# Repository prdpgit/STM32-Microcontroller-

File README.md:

# STM32 Microcontroller 
 
The designed PCB features an STM32F4RTG6 microcontroller which is part of the STM32F4 series known for its high performance and with floating point unit (FPU) that supports ARM Cortex-M4 core. The board integrates an MPU6050, which is a popular 6-axis MotionTracking device combining a 3-axis gyroscope and a 3-axis accelerometer.

## Microcontroller Core:

STM32F4RTG6: ARM Cortex-M4 core with FPU, running at high frequencies, capable of driving complex applications that require floating-point calculations and advanced control algorithms.
Sensors:

MPU6050: Offers onboard Digital Motion Processing™ (DMP™) capable of processing complex 6-axis MotionFusion algorithms. The sensors communicate via I2C protocol, which is set up on the STM32F4 microcontroller.
Power Supply:

The board appears to have a +5V input power supply, with onboard voltage regulation to provide +3.3V needed by both the STM32 microcontroller and the MPU6050 sensor.
Voltage regulators (like AMS1117-3.3) are used to step down the voltage.
Various capacitors are placed near power inputs and voltage regulators to stabilize the power supply and reduce noise.
Connectivity:

The microcontroller’s I/O pins are brought out to headers, providing the ability to connect to other peripherals and sensors.
The schematic shows decoupling capacitors and pull-up resistors on I2C lines which are critical for signal integrity.
Programming and Debugging Interface:

There appears to be a programming interface, possibly using Serial Wire Debug (SWD), which is standard for STM32 devices. This allows for programming and debugging of the microcontroller directly on the board.
Oscillator:

A crystal oscillator is used for providing an accurate clock signal to the STM32F4 microcontroller.
Load capacitors are connected to the crystal to ensure proper oscillation.
General PCB Design Notes:

The schematic is organized into functional blocks, which simplifies the complexity and helps in understanding the circuit.
Each IC has decoupling capacitors close to the power supply pins to reduce power supply noise and for maintaining signal integrity.
The use of pull-up resistors on the reset line and buttons indicates attention to proper microcontroller reset and user input handling.

## Schematic:

## PCB layout

## 3D PCB render

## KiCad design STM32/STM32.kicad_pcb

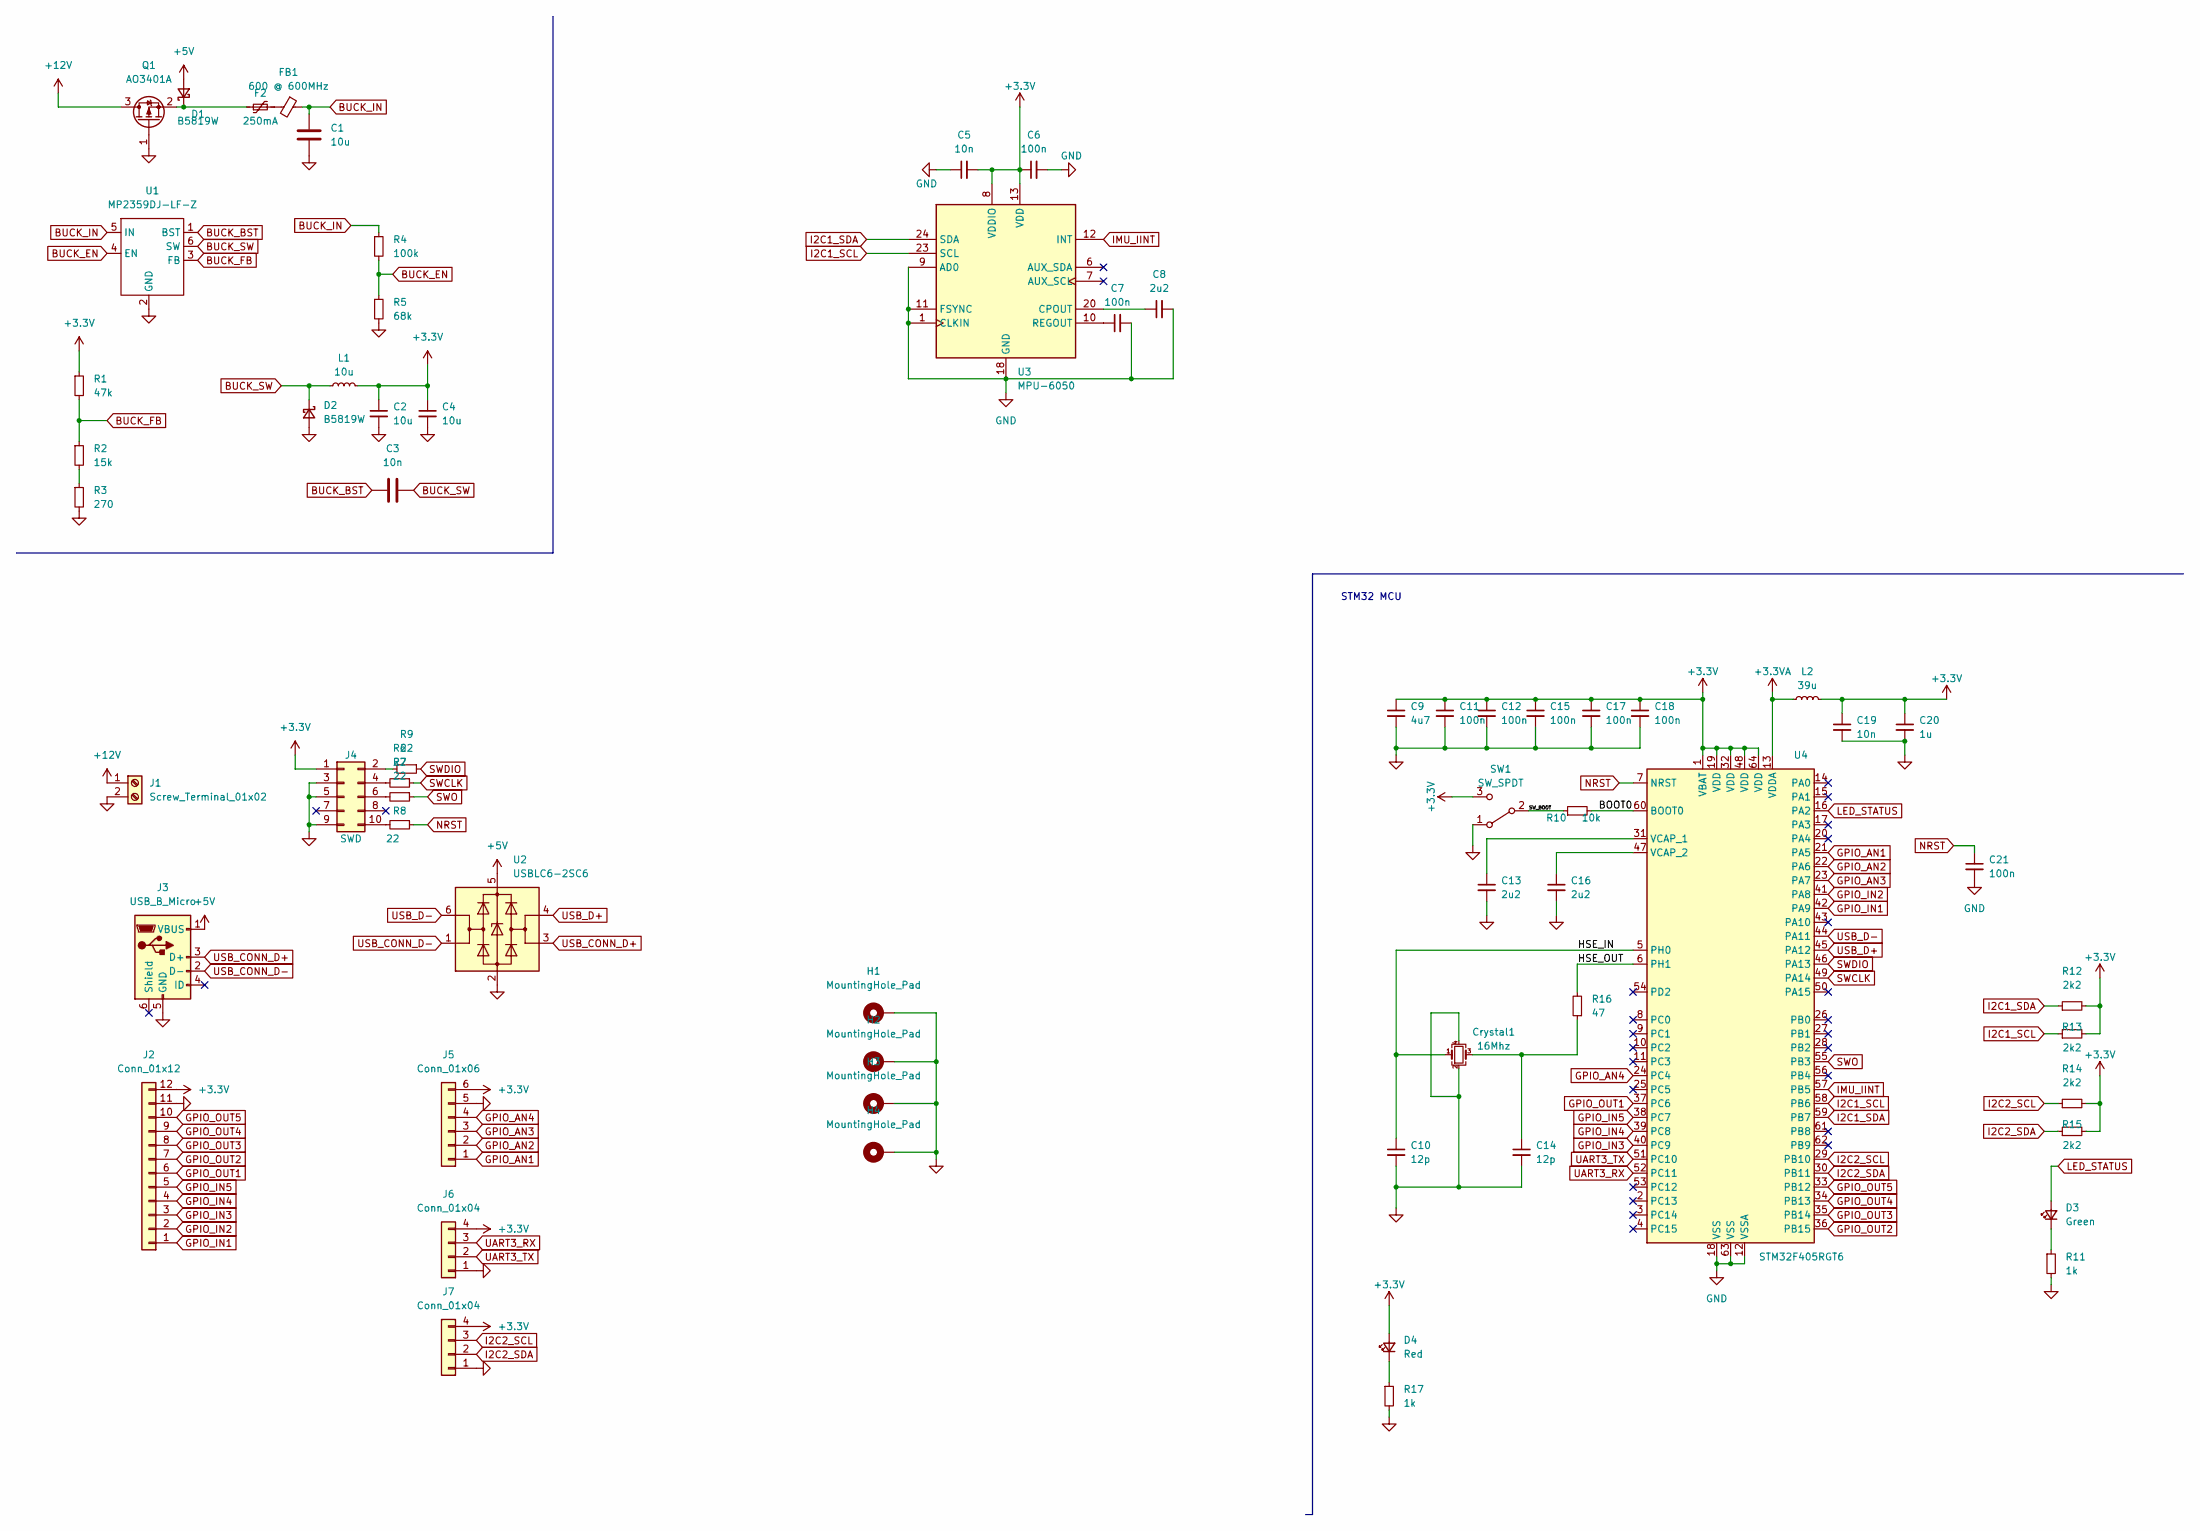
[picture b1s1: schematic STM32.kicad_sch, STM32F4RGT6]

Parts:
C1, C2, C4: 10u; C_1206_3216Metric; LCSC Part # C1954312
C3: 10n; C_1206_3216Metric; LCSC Part # C77497
C5: 10n; C_0603_1608Metric; LCSC Part # C2835533
C6, C7, C11, C12, C15, C17, C18, C21: 100n; C_0402_1005Metric; LCSC Part # C361203
C8, C13, C16: 2u2; C_0603_1608Metric; LCSC Part # C1953313
C9: 4u7; C_0603_1608Metric; LCSC Part # C2844393
C10, C14: 12p; C_0402_1005Metric; LCSC Part # C3876622
C19: 10n; C_0402_1005Metric; LCSC Part # C386111
C20: 1u; C_0402_1005Metric; LCSC Part # C1954072
Crystal1: 16Mhz; Crystal_SMD_3225-4Pin_3.2x2.5mm; LCSC Part # C160456
D1, D2: B5819W; D_SOD-123; LCSC Part # C779771
D3: Green; LED_0603_1608Metric; LCSC Part # C3148192
D4: Red; LED_0603_1608Metric; LCSC Part # C84263
F2: 250mA; Fuse_1206_3216Metric; LCSC Part # C369159
FB1: 600 @ 600MHz; L_0805_2012Metric; LCSC Part # C1017
H1, H2, H3, H4: MountingHole_Pad; MountingHole_4.3mm_M4_Pad_Via
J1: Screw_Terminal_01x02; TerminalBlock_Phoenix_PT-1,5-2-3.5-H_1x02_P3.50mm_Horizontal
J2: Conn_01x12; PinHeader_1x12_P2.54mm_Vertical
J3: USB_B_Micro; USB_Micro-B_Amphenol_10118194_Horizontal
J4: SWD; PinSocket_2x05_P1.27mm_Vertical_SMD
J5: Conn_01x06; PinHeader_1x06_P2.54mm_Vertical
J6, J7: Conn_01x04; PinHeader_1x04_P2.54mm_Vertical
L1: 10u; L_Sunlord_MWSA0518_5.4x5.2mm; LCSC Part # C139506
L2: 39u; L_0402_1005Metric; LCSC Part # C26443
Q1: AO3401A; SOT-23; LCSC Part # C306862
R1: 47k; R_0603_1608Metric; LCSC Part # C227501
R2: 15k; R_0603_1608Metric; LCSC Part # C3152125
R3: 270; R_0603_1608Metric; LCSC Part # C667461
R4: 100k; R_0603_1608Metric; LCSC Part # C667752
R5: 68k; R_0603_1608Metric; LCSC Part # C912142
R6, R7, R8, R9: 22; R_0402_1005Metric; LCSC Part # C174144
R10: 10k; R_0402_1005Metric; LCSC Part # C328298
R11, R17: 1k; R_0603_1608Metric; LCSC Part # C269704
R12, R13, R14, R15: 2k2; R_0402_1005Metric; LCSC Part # C3017487
R16: 47; R_0402_1005Metric; LCSC Part # C1096
SW1: SW_SPDT; SW_SPDT_PCM12
U1: MP2359DJ-LF-Z; SOT-23-6; LCSC Part # C14259
U2: USBLC6-2SC6; SOT-23-6
U3: MPU-6050; InvenSense_QFN-24_4x4mm_P0.5mm; LCSC Part # C24112
U4: STM32F405RGT6; LQFP-64_10x10mm_P0.5mm; LCSC Part # C15742

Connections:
+3.3V: C2.1, C4.1, C5.2, C6.1, C9.1, C11.1, C12.1, C15.1, C17.1, C18.1, C19.1, C20.1, D4.2 (A), J2.12, J4.1, J5.6, J6.4, J7.4, L1.2, L2.2, R1.1, R12.2, R13.2, R14.2, R15.2, SW1.3 (C), U3.8 (VDDIO), U3.13 (VDD), U4.1 (VBAT), U4.19 (VDD), U4.32 (VDD), U4.48 (VDD), U4.64 (VDD)
+3.3VA: L2.1, U4.13 (VDDA)
+5V: D1.2 (A), J3.1 (VBUS), U2.5 (VBUS)
+12V: J1.1, Q1.3 (D)
/BOOT0: R10.2, U4.60 (BOOT0)
/HSE_IN: C10.1, Crystal1.1, U4.5 (PH0)
/HSE_OUT: R16.2, U4.6 (PH1)
/SW_BOOT: R10.1, SW1.2 (B)
BUCK_BST: C3.1, U1.1 (BST)
BUCK_EN: R4.2, R5.1, U1.4 (EN)
BUCK_FB: R1.2, R2.1, U1.3 (FB)
BUCK_IN: C1.1, FB1.1, R4.1, U1.5 (IN)
BUCK_SW: C3.2, D2.1 (K), L1.1, U1.6 (SW)
GND: C1.2, C2.2, C4.2, C5.1, C6.2, C7.2, C8.2, C9.2, C10.2, C11.2, C12.2, C13.2, C14.2, C15.2, C16.2, C17.2, C18.2, C19.2, C20.2, C21.2, Crystal1.2, Crystal1.4, D2.2 (A), H1.1, H2.1, H3.1, H4.1, J1.2, J2.11, J3.5 (GND), J4.3, J4.5, J4.9, J5.5, J6.1, J7.1, Q1.1 (G), R3.2, R5.2, R11.2, R17.2, SW1.1 (A), U1.2 (GND), U2.2 (GND), U3.1 (CLKIN), U3.9 (AD0), U3.11 (FSYNC), U3.18 (GND), U4.12 (VSSA), U4.18 (VSS), U4.63 (VSS)
GPIO_AN1: J5.1, U4.21 (PA5)
GPIO_AN2: J5.2, U4.22 (PA6)
GPIO_AN3: J5.3, U4.23 (PA7)
GPIO_AN4: J5.4, U4.24 (PC4)
GPIO_IN1: J2.1, U4.42 (PA9)
GPIO_IN2: J2.2, U4.41 (PA8)
GPIO_IN3: J2.3, U4.40 (PC9)
GPIO_IN4: J2.4, U4.39 (PC8)
GPIO_IN5: J2.5, U4.38 (PC7)
GPIO_OUT1: J2.6, U4.37 (PC6)
GPIO_OUT2: J2.7, U4.36 (PB15)
GPIO_OUT3: J2.8, U4.35 (PB14)
GPIO_OUT4: J2.9, U4.34 (PB13)
GPIO_OUT5: J2.10, U4.33 (PB12)
I2C1_SCL: R13.1, U3.23 (SCL), U4.58 (PB6)
I2C1_SDA: R12.1, U3.24 (SDA), U4.59 (PB7)
I2C2_SCL: J7.3, R14.1, U4.29 (PB10)
I2C2_SDA: J7.2, R15.1, U4.30 (PB11)
IMU_IINT: U3.12 (INT), U4.57 (PB5)
LED_STATUS: D3.2 (A), U4.16 (PA2)
NRST: C21.1, R8.1, U4.7 (NRST)
unnamed: C7.1, U3.10 (REGOUT)
unnamed: C8.1, U3.20 (CPOUT)
unnamed: C13.1, U4.31 (VCAP_1)
unnamed: C14.1, Crystal1.3, R16.1
unnamed: C16.1, U4.47 (VCAP_2)
unnamed: D1.1 (K), F2.1, Q1.2 (S)
unnamed: D3.1 (K), R11.1
unnamed: D4.1 (K), R17.1
unnamed: F2.2, FB1.2
unnamed: J4.2, R9.2
unnamed: J4.4, R6.2
unnamed: J4.6, R7.2
unnamed: J4.10, R8.2
unnamed: R2.2, R3.1
SWCLK: R6.1, U4.49 (PA14)
SWDIO: R9.1, U4.46 (PA13)
SWO: R7.1, U4.55 (PB3)
UART3_RX: J6.3, U4.52 (PC11)
UART3_TX: J6.2, U4.51 (PC10)
USB_CONN_D+: J3.3 (D+), U2.3 (I/O2)
USB_CONN_D-: J3.2 (D-), U2.1 (I/O1)
USB_D+: U2.4 (I/O2), U4.45 (PA12)
USB_D-: U2.6 (I/O1), U4.44 (PA11)

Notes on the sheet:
STM32 MCU

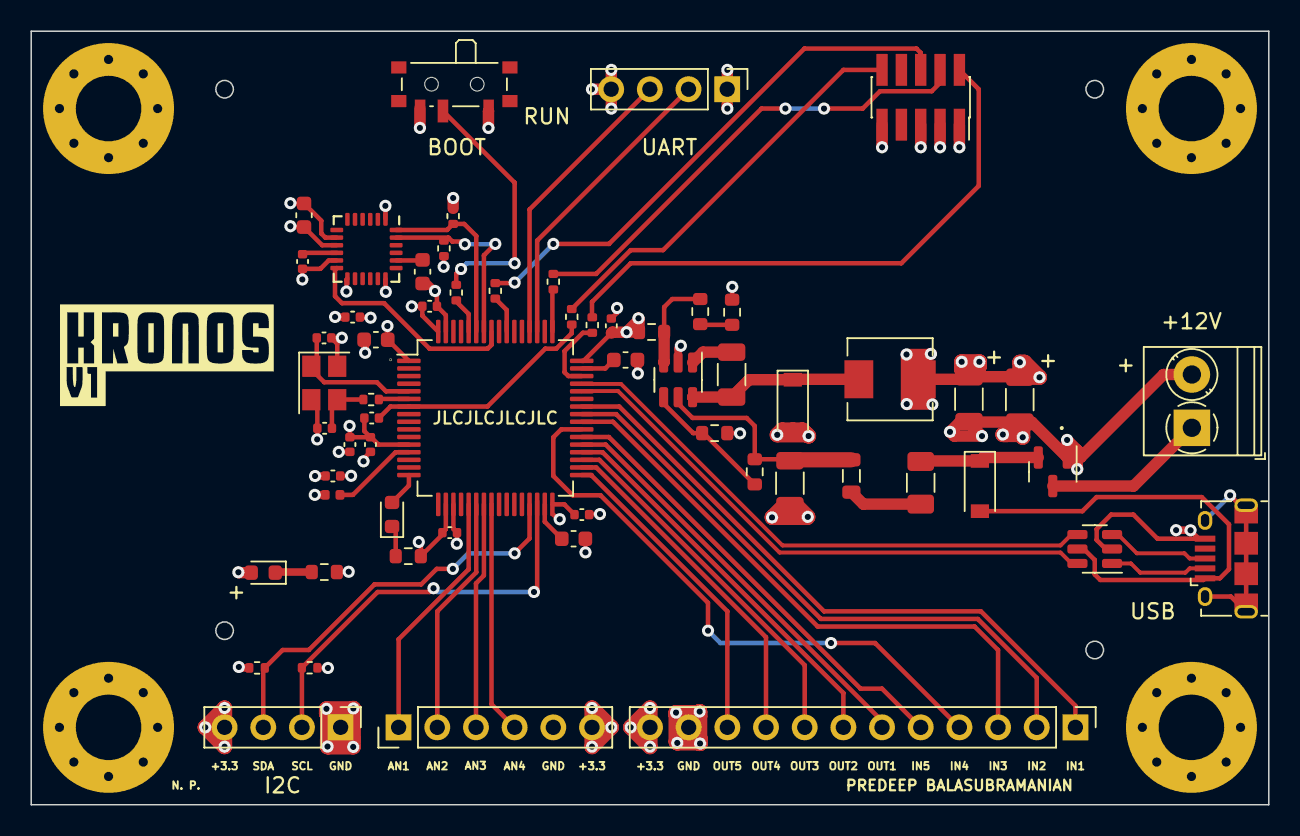
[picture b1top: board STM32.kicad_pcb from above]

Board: 4 copper layers, 81.3 x 50.8 mm, 64 parts (0 on the bottom side), 58 nets.

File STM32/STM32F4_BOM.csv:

Comment,Designator,Footprint,JLCPCB Part #
10u,C1,Capacitor_SMD:C_1206_3216Metric,C1954312
10u,"C2, C4",Capacitor_SMD:C_1206_3216Metric,C1954312
10n,C3,Capacitor_SMD:C_1206_3216Metric,C77497
10n,C5,Capacitor_SMD:C_0603_1608Metric,C2835533
100n,"C6, C7, C11, C12, C15, C17, C18, C21",Capacitor_SMD:C_0402_1005Metric,C361203
2u2,"C8, C13, C16",Capacitor_SMD:C_0603_1608Metric,C1953313
4u7,C9,Capacitor_SMD:C_0603_1608Metric,C2844393
12p,"C10, C14",Capacitor_SMD:C_0402_1005Metric,C76700
10n,C19,Capacitor_SMD:C_0402_1005Metric,C386111
1u,C20,Capacitor_SMD:C_0402_1005Metric,C913556
16Mhz,Crystal1,Crystal:Crystal_SMD_3225-4Pin_3.2x2.5mm,C160456
B5819W,"D1, D2",Diode_SMD:D_SOD-123,C779771
Green,D3,LED_SMD:LED_0603_1608Metric,C397049
Red,D4,LED_SMD:LED_0603_1608Metric,C90692
250mA,F2,Fuse:Fuse_1206_3216Metric,C369159
600 @ 600MHz,FB1,Inductor_SMD:L_0805_2012Metric,C1017
MountingHole_Pad,"H1, H2, H3, H4",MountingHole:MountingHole_4.3mm_M4_Pad_Via,
Screw_Terminal_01x02,J1,"TerminalBlock_Phoenix:TerminalBlock_Phoenix_PT-1,5-2-3.5-H_1x02_P3.50mm_Horizontal",
Conn_01x12,J2,Connector_PinHeader_2.54mm:PinHeader_1x12_P2.54mm_Vertical,
USB_B_Micro,J3,Connector_USB:USB_Micro-B_Amphenol_10118194_Horizontal,
SWD,J4,Connector_PinSocket_1.27mm:PinSocket_2x05_P1.27mm_Vertical_SMD,
Conn_01x06,J5,Connector_PinHeader_2.54mm:PinHeader_1x06_P2.54mm_Vertical,
Conn_01x04,"J6, J7",Connector_PinHeader_2.54mm:PinHeader_1x04_P2.54mm_Vertical,
10u,L1,Inductor_SMD:L_Sunlord_MWSA0518_5.4x5.2mm,C150031
39u,L2,Inductor_SMD:L_0402_1005Metric,C26443
AO3401A,Q1,Package_TO_SOT_SMD:SOT-23,C306862
47k,R1,Resistor_SMD:R_0603_1608Metric,C227501
15k,R2,Resistor_SMD:R_0603_1608Metric,C3152125
270,R3,Resistor_SMD:R_0603_1608Metric,C667461
100k,R4,Resistor_SMD:R_0603_1608Metric,C667752
68k,R5,Resistor_SMD:R_0603_1608Metric,C912142
22,"R6, R7, R8, R9",Resistor_SMD:R_0402_1005Metric,C174144
10k,R10,Resistor_SMD:R_0402_1005Metric,C328298
1k,"R11, R17",Resistor_SMD:R_0603_1608Metric,C269704
2k2,"R12, R13, R14, R15",Resistor_SMD:R_0402_1005Metric,C3017487
47,R16,Resistor_SMD:R_0402_1005Metric,C1096
SW_SPDT,SW1,Button_Switch_SMD:SW_SPDT_PCM12,
MP2359DJ-LF-Z,U1,Package_TO_SOT_SMD:SOT-23-6,C14259
USBLC6-2SC6,U2,Package_TO_SOT_SMD:SOT-23-6,
MPU-6050,U3,Sensor_Motion:InvenSense_QFN-24_4x4mm_P0.5mm,C24112
STM32F405RGT6,U4,Package_QFP:LQFP-64_10x10mm_P0.5mm,C15742

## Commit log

2022-07-16 New files
    New files added
2022-07-17 update
    NRST and BOOT0
2022-07-18 Schematics update
    New files and schematics
2022-09-14 Update STM32.kicad_sch
    changes
2022-12-29 change
